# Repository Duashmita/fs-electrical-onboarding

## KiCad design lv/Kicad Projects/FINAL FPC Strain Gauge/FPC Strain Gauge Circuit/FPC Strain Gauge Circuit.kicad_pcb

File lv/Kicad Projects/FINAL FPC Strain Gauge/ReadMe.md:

Overview:
This project is a temperature-compensated strain gauge using copper traces patterned directly onto a flexible PCB (FPC) to measure mechanical strain and vibrations.

The system converts strain-induced resistance changes into 24-bit digital measurements transmitted over SPI at a target of 1000 samples per second.

How It Works:

1. Copper Trace Strain Gauges

Two perpendicular sepentine copper traces act as resistive strain guages. Mechanical deformation changes their resistances and this is what we measure in terms of raw data.

2. Wheatstone Half-Bridge

The gauges and two resistors and two 350 ohm resistros form a Wheatstone brdige. Opposing resistance changes produce a differential voltage proportional to strain, while similar temperature effects largely cancel.

3. INA333 Amplifier

The INA333 amplifies the small differential voltage. A buffered 1.65 V reference offset is used here.

4. Analog Filtering

An RC low-pass filter is used to reduce high-frequency interference before digitization.

5. ADS1220IRVAR ADC

The Texas Instruments ADS1220IRVAR is a 24-bit delta-sigma ADC in a 3.5 × 3.5 mm VQFN-16 package.
 
    a. Measures LOAD_SIGNAL relative to VREF_1V65
    b. Uses a 2.048 V internal reference
    c. Provides internal digital filtering
    d. Configured for 1 kS/s continuous conversion
    e. Operates from the board's 3.3 V supply

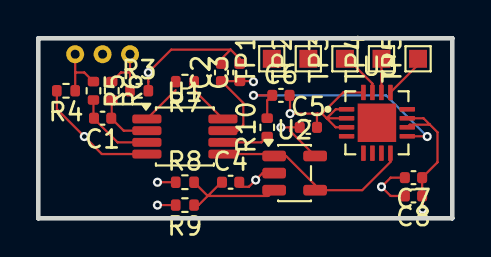
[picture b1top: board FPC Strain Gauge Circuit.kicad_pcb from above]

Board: 4 copper layers, 23.0 x 10.0 mm, 24 parts (0 on the bottom side), 15 nets.

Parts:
C1, C6: 10nF; C_0402_1005Metric
C2, C5, C7, C8: 100nF; C_0402_1005Metric
C3, C4: 1uF; C_0402_1005Metric
R3, R4: 350; R_0402_1005Metric
R5, R6: 100; R_0402_1005Metric
R7, R10: 1k; R_0402_1005Metric
R8, R9: 10k; R_0402_1005Metric
TP1, TP2, TP3, TP4, TP5: TestPoint; TestPoint_Pad_1.0x1.0mm
U1: INA333xxDGK; VSSOP-8_3x3mm_P0.65mm
U2: OPA333xxDBV; SOT-23-5
U3: ADS1220IRVAR; QFN50P350X350X100-17N

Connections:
+3V3_A: C2.1, C3.1, C5.1, C7.1, C8.1, R8.1, TP1.1 (1_1), U1.7 (V+), U2.5 (V+), U3.10 (AVDD), U3.11 (DVDD)
/ADC_MISO: TP5.1 (1_1), U3.13 (DOUT/DRDY)
/ADC_MOSI: TP4.1 (1_1), U3.14 (DIN)
/ADC_SCLK: TP3.1 (1_1), U3.15 (SCLK)
/LOAD_SIGNAL: C6.1, R10.2, U3.9 (ALNO/REFP1)
/VREF_1V65: U1.5 (Ref), U2.1, U2.4 (-), U3.8 (AIN1)
/VREF_RAW: C4.1, R8.2, R9.1, U2.3 (+)
AGND: C2.2, C3.2, C4.2, C5.2, C6.2, C7.2, C8.2, R3.2, R4.2, R9.2, TP2.1 (1_1), U1.4 (V-), U2.2 (V-), U3.1 (CLK), U3.2 (DGND), U3.3 (AVSS), U3.16 (CS)
unnamed: R7.1, U1.8 (Rg)
unnamed: R7.2, U1.1 (Rg)
unnamed: R10.1, U1.6
unnamed: C1.2, R5.2, U1.3 (+)
unnamed: C1.1, R6.2, U1.2 (-)
R1: R3.1, R6.1
R2: R4.1, R5.1

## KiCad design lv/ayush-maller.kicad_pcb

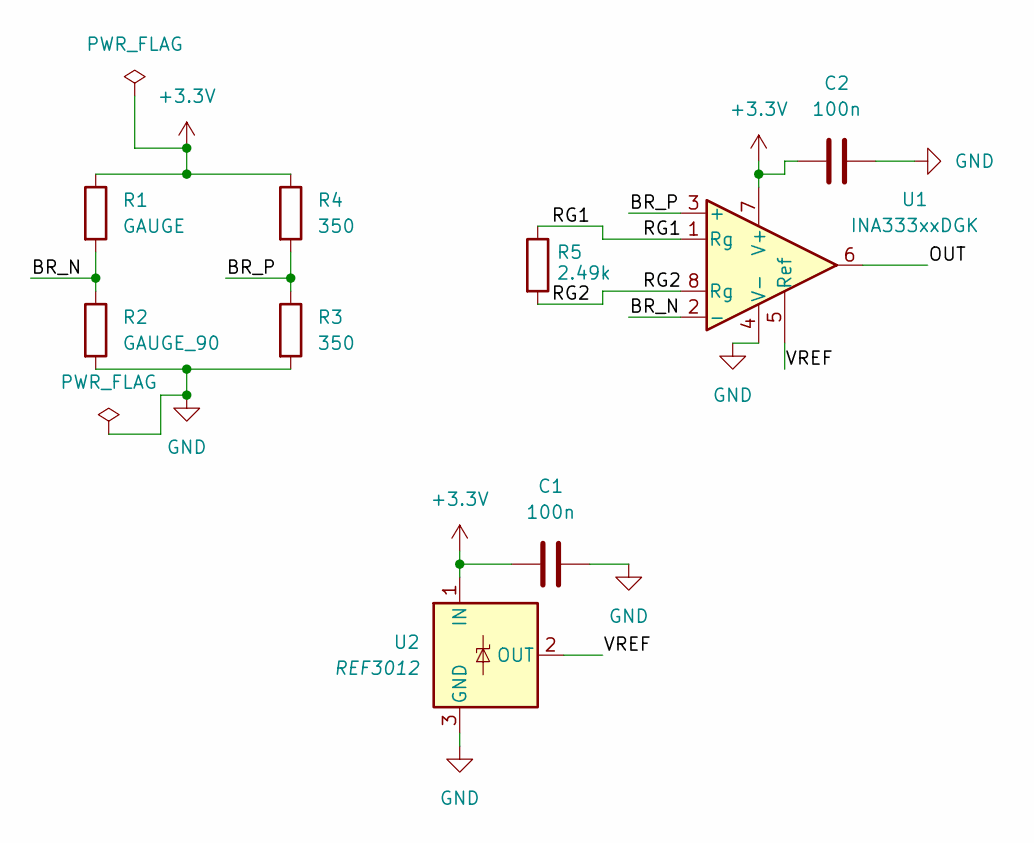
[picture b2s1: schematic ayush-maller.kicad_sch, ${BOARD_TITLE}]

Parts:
C1, C2: 100n; C_0603_1608Metric
R1: GAUGE; PinHeader_1x02_P2.54mm_Vertical
R2: GAUGE_90; PinHeader_1x02_P2.54mm_Vertical
R3, R4: 350; R_0603_1608Metric
R5: 2.49k; R_0603_1608Metric
U1: INA333xxDGK; VSSOP-8_3x3mm_P0.65mm
U2: REF3012; SOT-23

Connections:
+3.3V: C1.1, C2.2, R1.1, R4.1, U1.7 (V+), U2.1 (IN)
/BR_N: R1.2, R2.1, U1.2 (-)
/BR_P: R3.1, R4.2, U1.3 (+)
/OUT: U1.6
/RG1: R5.1, U1.1 (Rg)
/RG2: R5.2, U1.8 (Rg)
/VREF: U1.5 (Ref), U2.2 (OUT)
GND: C1.2, C2.1, R2.2, R3.2, U1.4 (V-), U2.3 (GND)

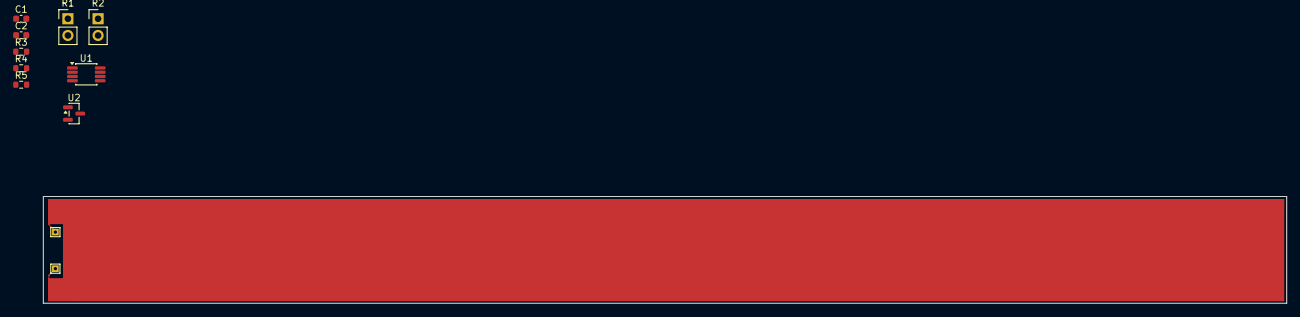
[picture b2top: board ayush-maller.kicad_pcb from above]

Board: 2 copper layers, 189.1 x 16.2 mm, 9 parts (0 on the bottom side), 7 nets.

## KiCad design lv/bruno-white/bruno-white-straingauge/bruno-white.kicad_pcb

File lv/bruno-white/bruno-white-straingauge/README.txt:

KiCad Local History Directory
=============================

Hello Luca, here are my notes that I have taken for LV:
https://docs.google.com/document/d/1vGJ4rhs0kplqLNoltI60dMivU1lJGl6AMdztJyYFMIQ/edit?usp=sharing

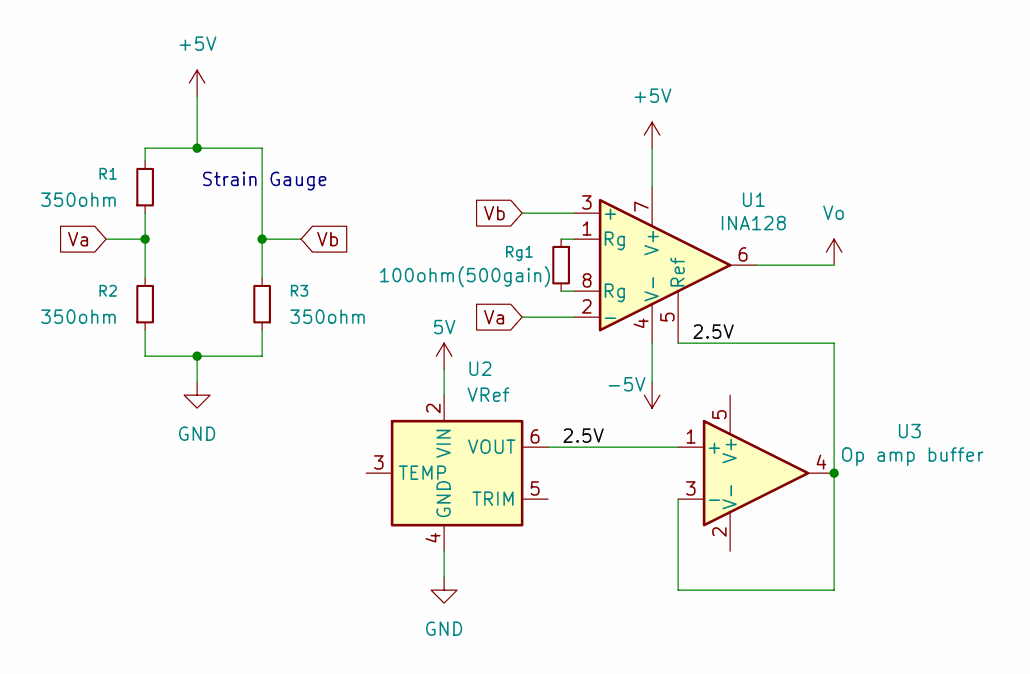
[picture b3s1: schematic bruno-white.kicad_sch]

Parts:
R1, R2, R3: 350ohm; R_0603_1608Metric_Pad0.98x0.95mm_HandSolder
Rg1: 100ohm(500gain); R_0603_1608Metric_Pad0.98x0.95mm_HandSolder
U1: INA128; VSSOP-8_3x3mm_P0.65mm
U2: VRef; SOIC-8_3.9x4.9mm_P1.27mm
U3: Op amp buffer; SOT-353_SC-70-5

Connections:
5V: U2.2 (VIN)
-5V: U1.4 (V-)
/2.5V: U1.5 (Ref), U2.6 (VOUT), U3.1 (+), U3.3 (-), U3.4
GND: R2.1, R3.1, U2.4 (GND)
unnamed: Rg1.1, U1.1 (Rg)
unnamed: Rg1.2, U1.8 (Rg)
Va: R1.1, R2.2, U1.2 (-)
Vb: R1.2, R3.2, U1.3 (+), U1.7 (V+); also elsewhere on the board
Vo: U1.6

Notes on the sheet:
Strain Gauge

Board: 2 copper layers, 8 parts (0 on the bottom side), 6 nets, no tracks yet.

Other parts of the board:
SG1: 350ohm; SolderWire-0.5sqmm_1x01_D0.9mm_OD2.1mm

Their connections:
Vb: SG1.1; also elsewhere on the board

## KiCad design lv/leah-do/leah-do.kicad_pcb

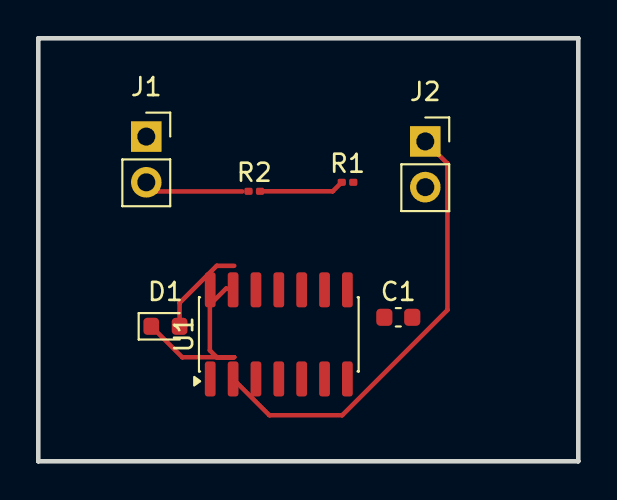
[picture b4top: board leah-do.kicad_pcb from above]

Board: 2 copper layers, 30.0 x 23.5 mm, 7 parts (0 on the bottom side), 6 nets.

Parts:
C1: 10nF; C_0603_1608Metric
D1: D_Small; D_0603_1608Metric
J1: TS_IN; PinSocket_1x02_P2.54mm_Vertical
J2: PK_HOLD_OUT; PinSocket_1x02_P2.54mm_Vertical
R1: 1k; R_0201_0603Metric
R2: 24k; R_0201_0603Metric
U1: MCP6004; SOIC-14_3.9x8.7mm_P1.27mm

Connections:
/PK_HOLD_VAL: J2.1, U1.6 (-), U1.7
/TS+: J1.2, R2.1
GND: C1.2, J1.1, J2.2, R1.2
unnamed: D1.2 (A), U1.1
unnamed: C1.1, D1.1 (K), U1.2 (-), U1.5 (+)
unnamed: R1.1, R2.2, U1.3 (+)
